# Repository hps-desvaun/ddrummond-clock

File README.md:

# ddrummond-clock
 My First HPS Clock

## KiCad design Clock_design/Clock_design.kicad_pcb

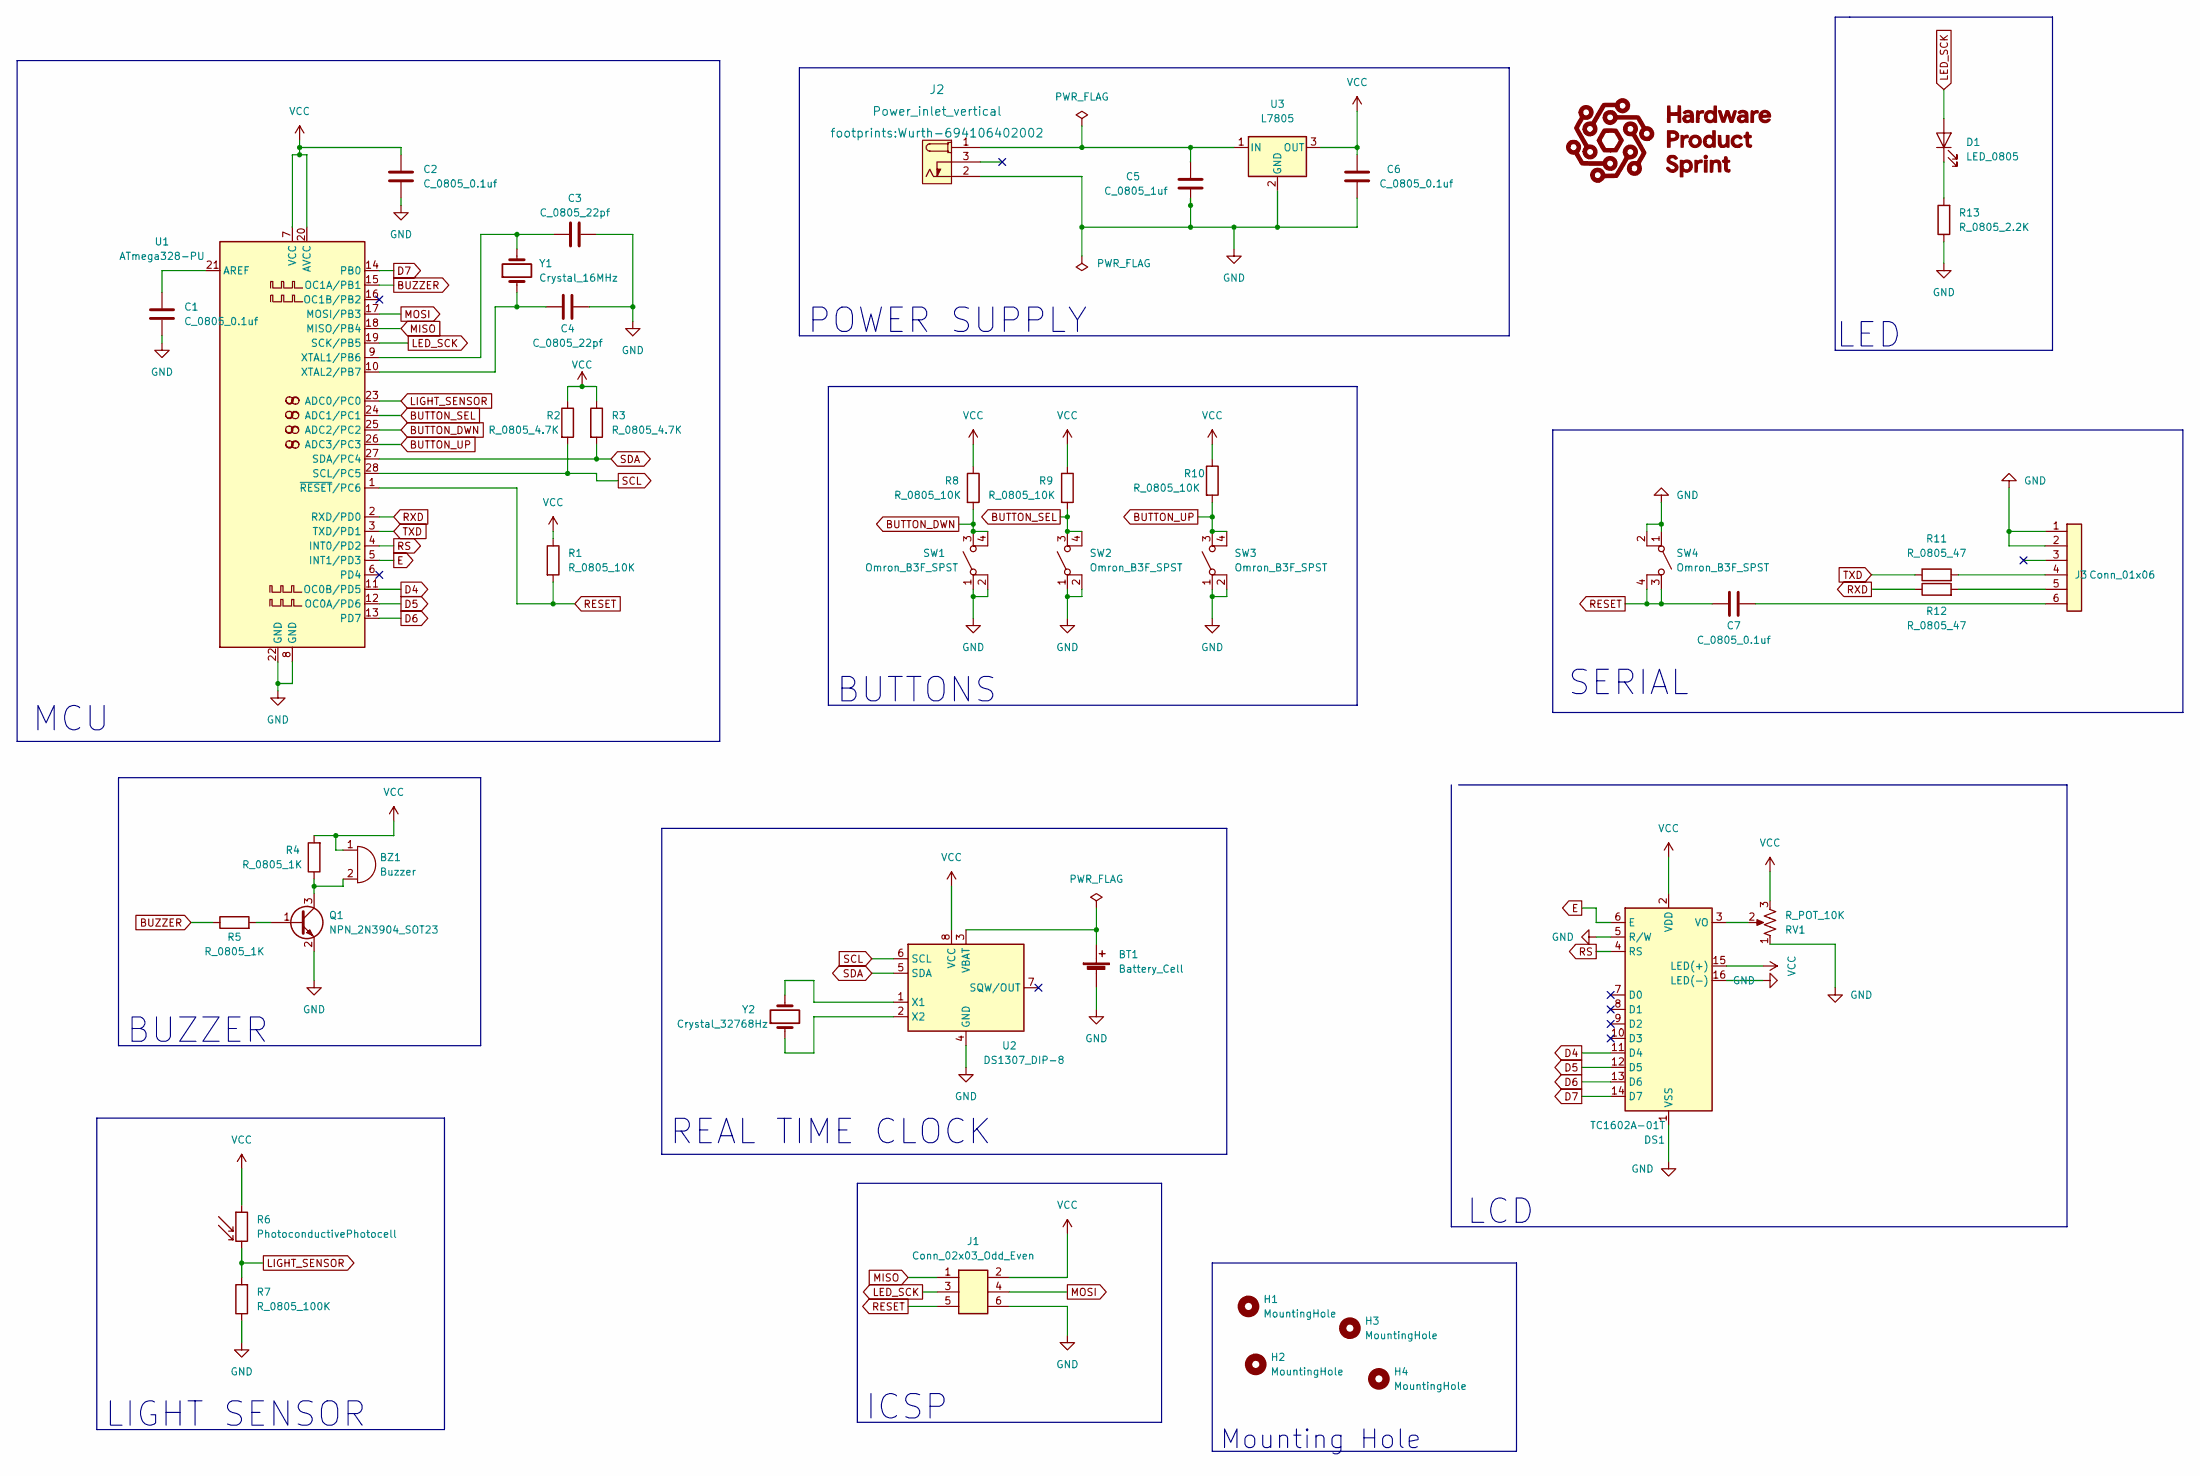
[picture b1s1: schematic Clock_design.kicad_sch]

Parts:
BT1: Battery_Cell; BatteryHolder_Keystone_106_1x20mm; MPN BS-7; Digikey PN BS-7-ND
BZ1: Buzzer; Buzzer_TDK_PS1240P02BT_D12.2mm_H6.5mm; MPN PS1420P02CT; Digikey PN 445-2526-1-ND
C1, C2, C6, C7: C_0805_0.1uf; C_0805_2012Metric; Voltage N/A; Tolerance N/A; MPN 08055C104KAT2A; Digikey PN 478-1395-1-ND
C3, C4: C_0805_22pf; C_0805_2012Metric; Voltage N/A; Tolerance N/A; MPN CC0805JRNPO9BN220; Digikey PN 311-1103-1-ND
C5: C_0805_1uf; C_0805_2012Metric; Voltage N/A; Tolerance N/A; MPN CC0805KKX7R8BB105; Digikey PN 311-1456-1-ND
D1: LED_0805; LED_0805_2012Metric; MPN 150080RS75000; Digikey PN 732-4984-1-ND
DS1: TC1602A-01T; MPN 1447; Digikey PN 1528-2212-ND
H1, H2, H3, H4: MountingHole; MountingHole_3.2mm_M3
J1: Conn_02x03_Odd_Even; PinHeader_2x03_P2.54mm_Vertical; MPN PRPC003DAAN-RC; Digikey PN S2011EC-03-ND
J2: Power_inlet_vertical; Wurth-694106402002; MPN 694106402002; Digikey PN 732-5931-ND
J3: Conn_01x06; PinHeader_1x06_P2.54mm_Vertical; MPN 61300611121; Digikey PN 732-5319-ND
Q1: NPN_2N3904_SOT23; SOT-23; MPN CMPT3904E TR PBFREE; Digikey PN 1514-CMPT3904ETRPBFREECT-ND
R1, R8, R9, R10: R_0805_10K; R_0805_2012Metric; Tolerance N/A; MPN RC0805FR-0710KL; Digikey PN 311-10.0KCRCT-ND
R2, R3: R_0805_4.7K; R_0805_2012Metric; Tolerance N/A; MPN RC0805FR-074K7L; Digikey PN 311-4.70KCRCT-ND
R4, R5: R_0805_1K; R_0805_2012Metric; Tolerance N/A; Mouser PN N/A; Digikey PN RC0805FR-0710KL
R6: PhotoconductivePhotocell; R_LDR_4.9x4.2mm_P2.54mm_Vertical; Voltage N/A; Tolerance N/A; MPN PDV-P8103; Digikey PN PDV-P8103-ND
R7: R_0805_100K; R_0805_2012Metric; Tolerance N/A; MPN RC0805FR-07100KL; Digikey PN 311-100KCRCT-ND
R11, R12: R_0805_47; R_0805_2012Metric; Tolerance N/A; Mouser PN N/A; Digikey PN RC0805FR-0747RL
R13: R_0805_2.2K; R_0805_2012Metric; Tolerance N/A; MPN N/A; Digikey PN 311-2.20KCRCT-ND
RV1: R_POT_10K; Potentiometer_Bourns_3386P_Vertical; MPN 3386P-1-103TLF; Digikey PN 3386P-103TLF-ND
SW1, SW2, SW3, SW4: Omron_B3F_SPST; SW_SPST_Omron_B3FS-100xP; MPN B3FS-1000P; Digikey PN SW423CT-ND
U1: ATmega328-PU; DIP-28_W7.62mm; MPN ED281DT; Digikey PN ED3050-5-ND
U2: DS1307_DIP-8; DIP-8_W7.62mm; MPN A 08-LC-TT; Digikey PN AE9986-ND
U3: L7805; TO-252-2; MPN L7805CDT-TR; Digikey PN 497-7255-1-ND
Y1: Crystal_16MHz; Crystal_SMD_HC49-SD; MPN ECS-160-20-5PXDN-TR; Digikey PN XC1299CT-ND
Y2: Crystal_32768Hz; Crystal_SMD_2Pin_3.2x1.5mm; MPN Q 0,032768-JTX310-12,5-20-T1-HMR-50K-LF; Digikey PN 1908-1314-1-ND

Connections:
BUTTON_DWN: R8.2, SW1.3 (B), SW1.4 (B), U1.25 (ADC2/PC2)
BUTTON_SEL: R9.2, SW2.3 (B), SW2.4 (B), U1.24 (ADC1/PC1)
BUTTON_UP: R10.2, SW3.3 (B), SW3.4 (B), U1.26 (ADC3/PC3)
BUZZER: R5.1, U1.15 (OC1A/PB1)
D4: DS1.11 (D4), U1.11 (OC0B/PD5)
D5: DS1.12 (D5), U1.12 (OC0A/PD6)
D6: DS1.13 (D6), U1.13 (PD7)
D7: DS1.14 (D7), U1.14 (PB0)
E: DS1.6 (E), U1.5 (INT1/PD3)
GND: BT1.2 (-), C1.2, C2.2, C3.2, C4.2, C5.2, C6.2, DS1.1 (VSS), DS1.5 (R/W), DS1.16 (LED(-)), J1.6, J2.2 (OUT), J3.1, J3.2, Q1.2 (E), R7.1, R13.1, RV1.1, SW1.1 (A), SW1.2 (A), SW2.1 (A), SW2.2 (A), SW3.1 (A), SW3.2 (A), SW4.1 (A), SW4.2 (A), U1.8 (GND), U1.22 (GND), U2.4 (GND), U3.2 (GND)
LED_SCK: D1.2 (A), J1.3, U1.19 (SCK/PB5)
LIGHT_SENSOR: R6.2, R7.2, U1.23 (ADC0/PC0)
MISO: J1.1, U1.18 (MISO/PB4)
MOSI: J1.4, U1.17 (MOSI/PB3)
unnamed: BT1.1 (+), U2.3 (VBAT)
unnamed: BZ1.2 (+), Q1.3 (C), R4.1
unnamed: C1.1, U1.21 (AREF)
unnamed: C3.1, U1.9 (XTAL1/PB6), Y1.2
unnamed: C4.1, U1.10 (XTAL2/PB7), Y1.1
unnamed: C5.1, J2.1 (POLE), U3.1 (IN)
unnamed: C7.2, J3.6
unnamed: D1.1 (K), R13.2
unnamed: DS1.3 (VO), RV1.2
unnamed: J3.4, R11.2
unnamed: J3.5, R12.2
unnamed: Q1.1 (B), R5.2
unnamed: U2.1 (X1), Y2.2
unnamed: U2.2 (X2), Y2.1
RESET: C7.1, J1.5, R1.2, SW4.3 (B), SW4.4 (B), U1.1 (~RESET/PC6)
RS: DS1.4 (RS), U1.4 (INT0/PD2)
RXD: R12.1, U1.2 (RXD/PD0)
SCL: R2.2, U1.28 (SCL/PC5), U2.6 (SCL)
SDA: R3.2, U1.27 (SDA/PC4), U2.5 (SDA)
TXD: R11.1, U1.3 (TXD/PD1)
VCC: BZ1.1 (-), C2.1, C6.1, DS1.2 (VDD), DS1.15 (LED(+)), J1.2, R1.1, R2.1, R3.1, R4.2, R6.1, R8.1, R9.1, R10.1, RV1.3, U1.7 (VCC), U1.20 (AVCC), U2.8 (VCC), U3.3 (OUT)

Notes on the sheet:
LIGHT SENSOR
ICSP
BUTTONS
BUZZER
LED
POWER SUPPLY
MCU
REAL TIME CLOCK
Mounting Hole
LCD
SERIAL

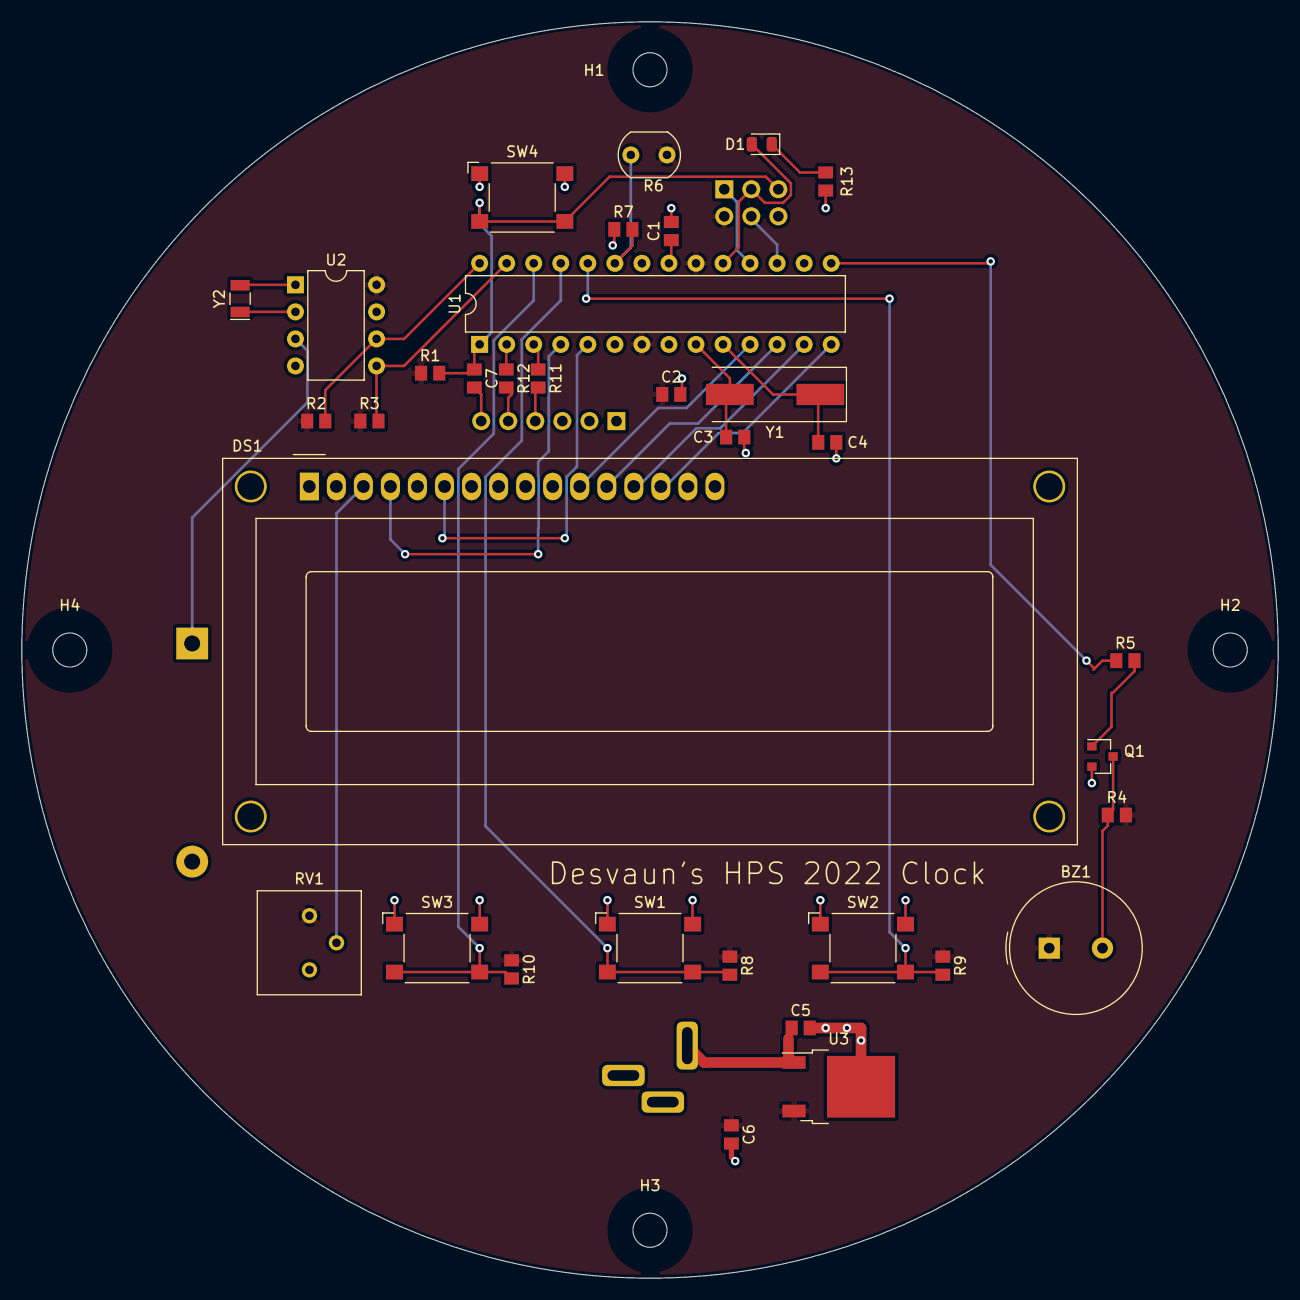
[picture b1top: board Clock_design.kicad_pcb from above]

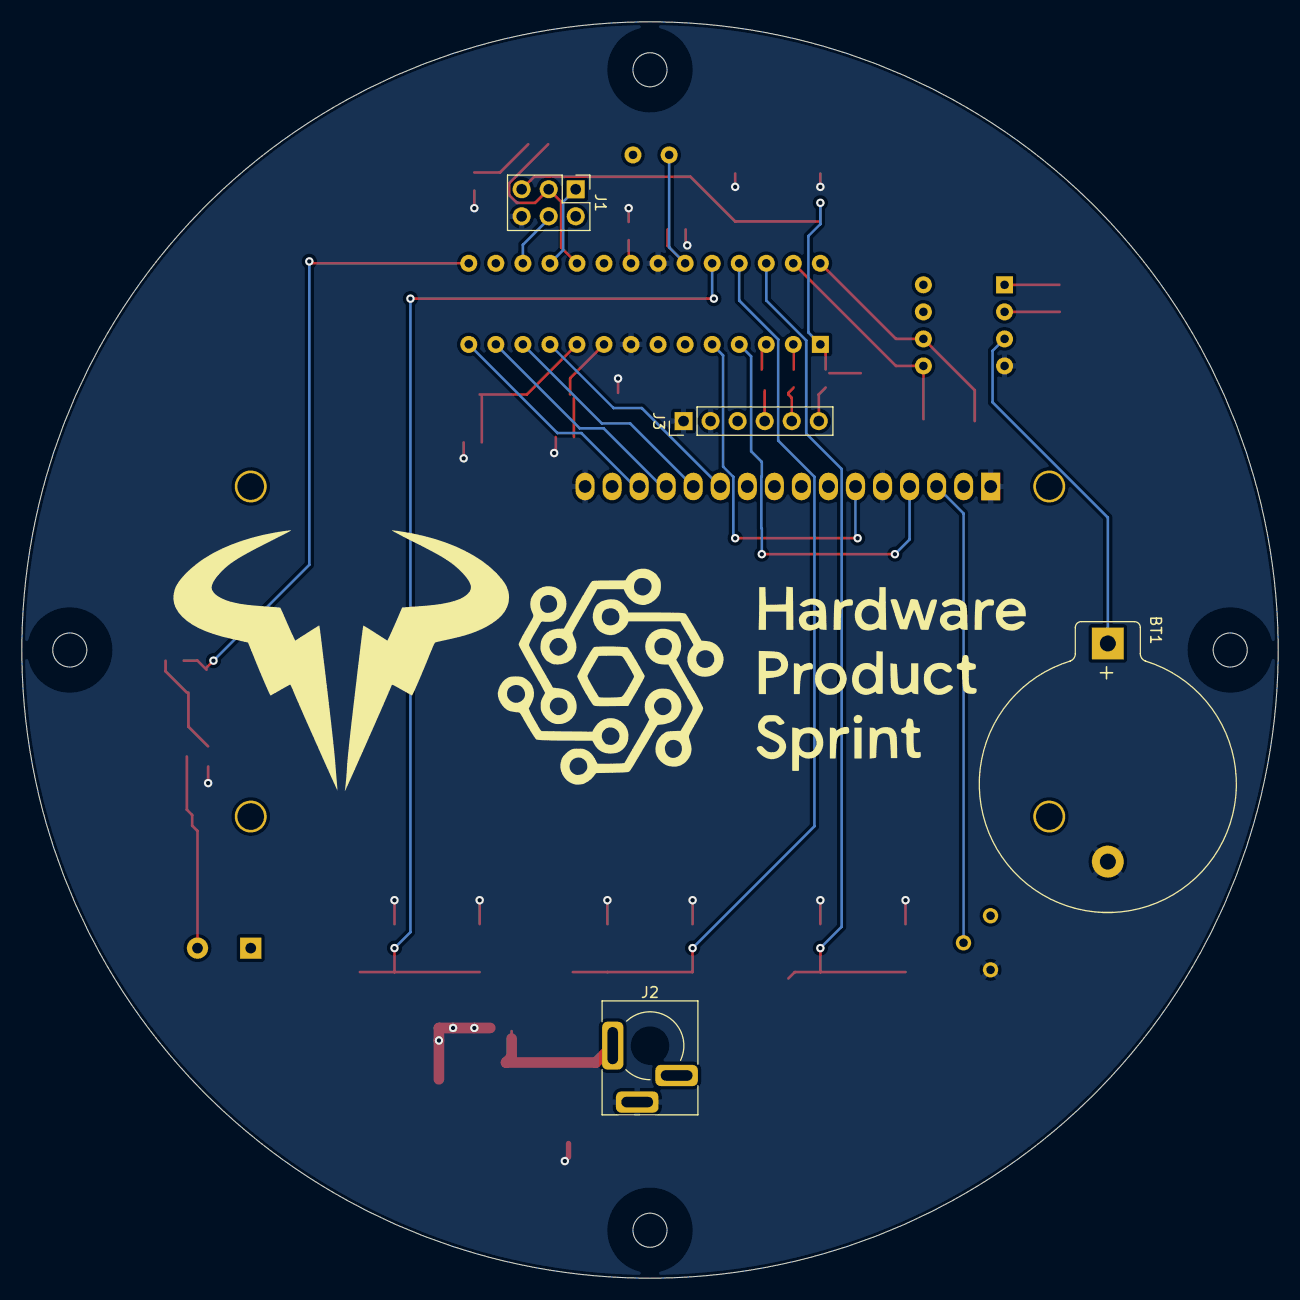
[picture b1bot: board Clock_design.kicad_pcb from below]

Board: 2 copper layers, 118.0 x 118.0 mm, 42 parts (4 on the bottom side), 35 nets.

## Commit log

2022-06-05 My First Design Commit
2022-07-24 Layout Complete!
2022-07-24 Routing done
2022-07-25 Routing done Update 2
2022-07-25 Routing Update 3
2022-07-25 Routing Update 4
2022-07-26 Final Gerber Out
